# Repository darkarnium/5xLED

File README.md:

# 5xLED
Five LED 'business' cards. Intended for use with WS2812B RGB LEDs, and an ATtiny85.

## Caveats
This is my first attempt at OSS hardware, so it's probably awful. Feel free to PR in! :)

## BOM
To follow.

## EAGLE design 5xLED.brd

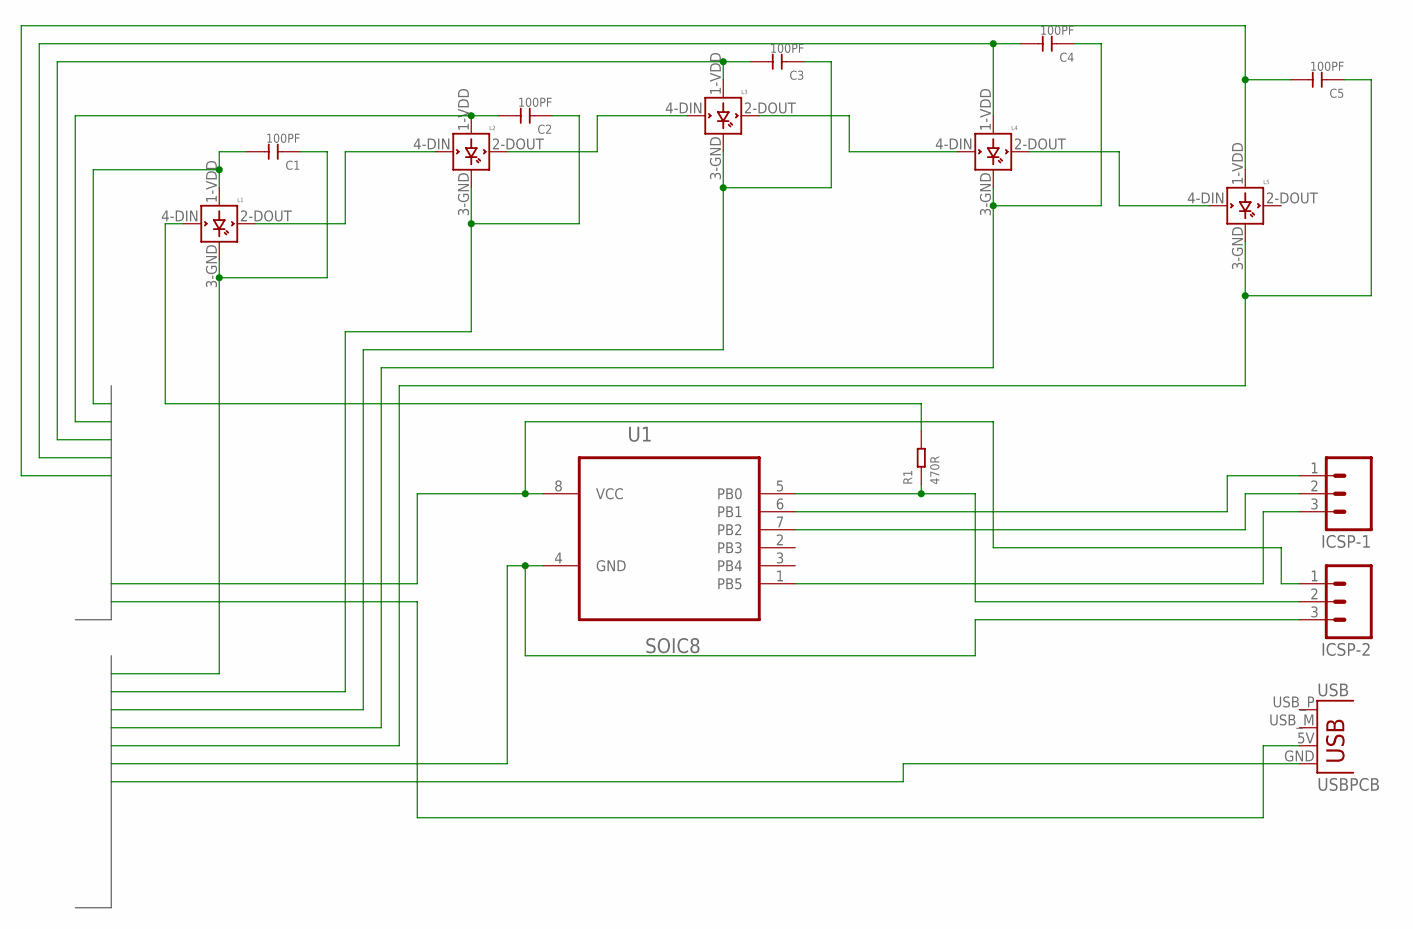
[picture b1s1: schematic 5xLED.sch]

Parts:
C1, C2, C3, C4, C5: 100PF; C0805
ICSP-1, ICSP-2: M03SMD_RA_MALE; 1X03_SMD_RA_MALE
L1, L2, L3, L4, L5: WS2812B
R1: 470R; R0805
U1: SOIC8; SOIC8-1.27-5.3X5.3MM
USB: USBPCB; USB-A-PCB

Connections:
GND: C1.1, C2.1, C3.1, C4.1, C5.1, ICSP-2.3, L1.3-GND (GND), L2.3-GND (GND), L3.3-GND (GND), L4.3-GND (GND), L5.3-GND (GND), U1.4 (GND), USB.GND
unnamed: L1.2-DOUT (DOUT), L2.4-DIN (DIN)
unnamed: L2.2-DOUT (DOUT), L3.4-DIN (DIN)
unnamed: L3.2-DOUT (DOUT), L4.4-DIN (DIN)
unnamed: L4.2-DOUT (DOUT), L5.4-DIN (DIN)
unnamed: ICSP-2.2, R1.1, U1.5 (PB0)
unnamed: ICSP-1.1, U1.6 (PB1)
unnamed: ICSP-1.2, U1.7 (PB2)
unnamed: ICSP-1.3, U1.1 (PB5)
unnamed: L1.4-DIN (DIN), R1.2
VCC: C1.2, C2.2, C3.2, C4.2, C5.2, ICSP-2.1, L1.1-VDD (VDD), L2.1-VDD (VDD), L3.1-VDD (VDD), L4.1-VDD (VDD), L5.1-VDD (VDD), U1.8 (VCC), USB.5V (VBUS)

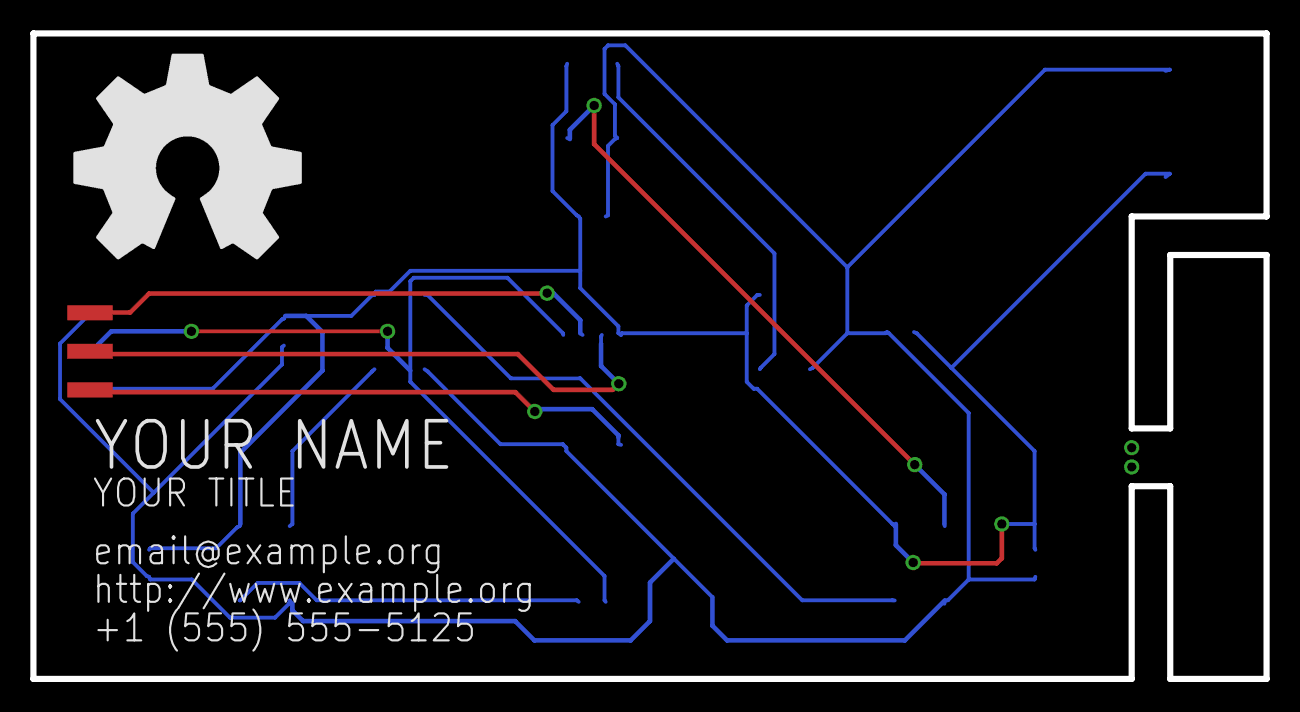
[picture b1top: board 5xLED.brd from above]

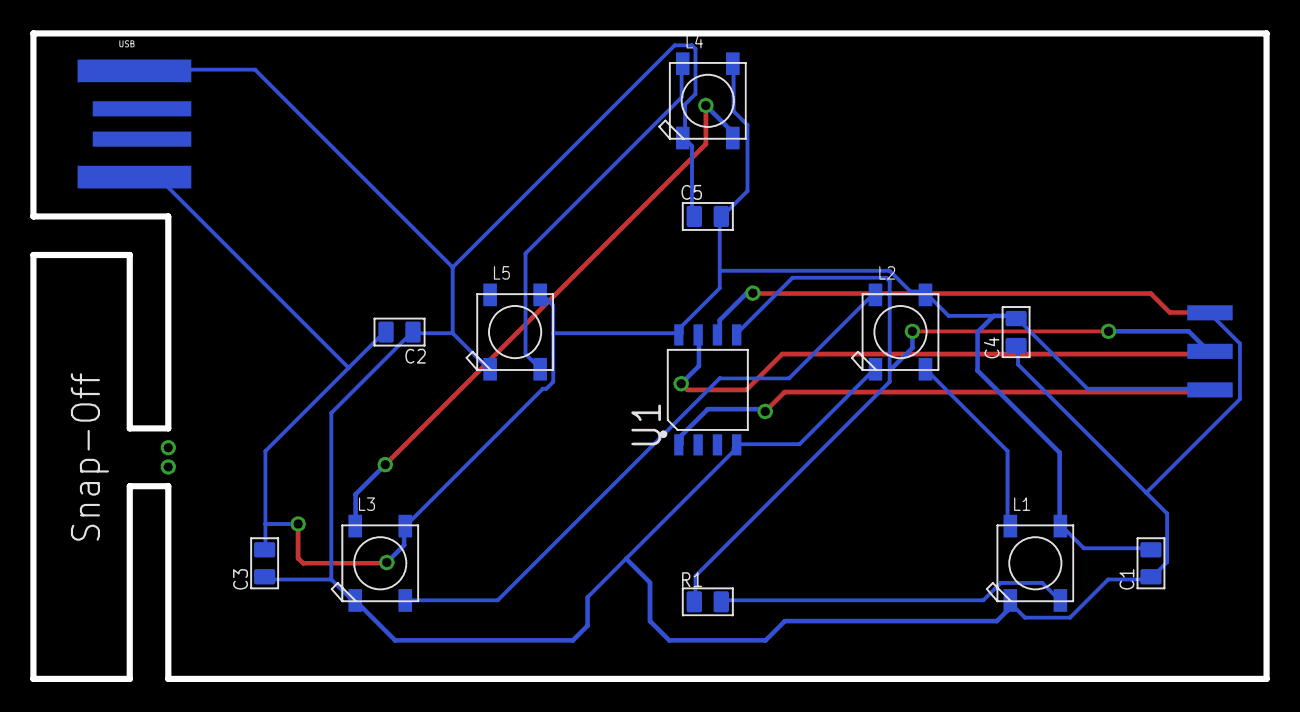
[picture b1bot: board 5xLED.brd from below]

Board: 2 copper layers, 81.3 x 42.5 mm, 15 parts (14 on the bottom side), 11 nets.

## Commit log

2015-10-09 Initial commit of EAGLE schematic and PCB layout.

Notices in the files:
parts and their libraries:
SparkFun-Connectors: Licensing: Creative Commons ShareAlike 4.0 International - https://creativecommons.org/licenses/by-sa/4.0
